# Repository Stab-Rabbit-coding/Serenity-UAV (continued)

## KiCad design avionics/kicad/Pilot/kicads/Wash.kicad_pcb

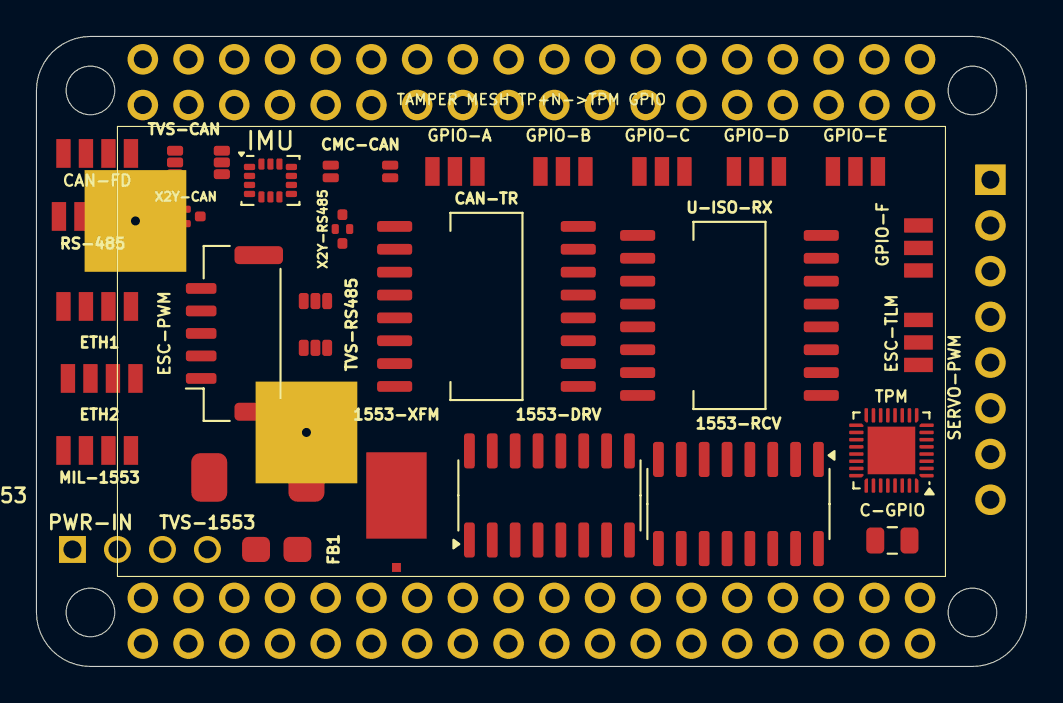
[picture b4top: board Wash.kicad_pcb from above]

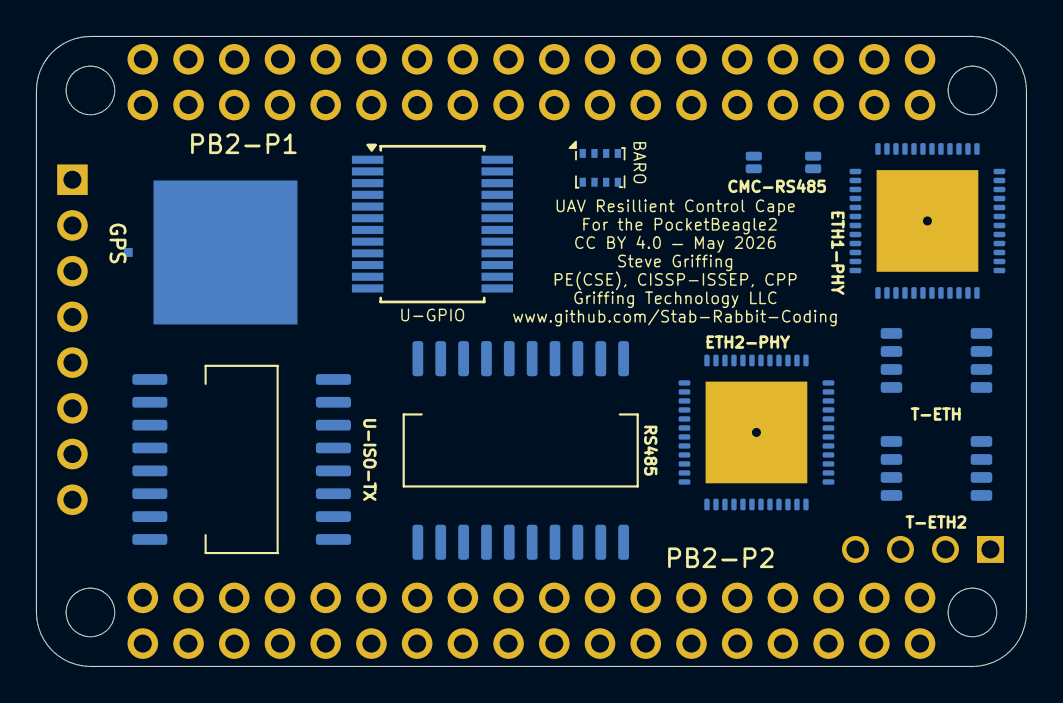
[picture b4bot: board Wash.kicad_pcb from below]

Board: 4 copper layers, 55.0 x 35.0 mm, 42 parts (12 on the bottom side), 83 nets, no tracks yet.

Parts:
1553-DRV: DS26LV31; SOIC-16_3.9x9.9mm_P1.27mm
1553-RCV: DS26LV32; SOIC-16_3.9x9.9mm_P1.27mm
1553-XFM: SM-1553-11; Package
BARO: BMP388; Bosch_LGA-8_2x2.5mm_P0.65mm_ClockwisePinNumbering
C-GPIO: 100nF; C_0805_2012Metric
CAN-FD: JST-GH-4P-CAN; JST_GH_4P
CAN-TR: ISOW1044BDFMR; SOIC-16W_7.5x10.3mm_P1.27mm
CMC-CAN: SRF2012-100Y; Bourns_SRF2012_4T
CMC-RS485: SRF2012-100Y; Bourns_SRF2012_4T
ESC-PWM: JST-GH-5P-ESC; JST_GH_SM05B-GHS-TB_1x05-1MP_P1.25mm_Horizontal
ESC-TLM: JST-GH-3P-ESC-TELEM; JST_GH_3P
ETH1, ETH2: JST-GH-4P-ETH; JST_GH_4P
ETH1-PHY, ETH2-PHY: ADIN1300BCPZ; QFN-48-1EP_7x7mm_P0.5mm_EP5.65x5.65mm
FB1: 742792512; C_0805_2012Metric
GPIO-A: JST-GH-3P-GPIO; JST_GH_3P_V
GPIO-B: JST-GH-3P-GPIO; JST_GH_3P_V
GPIO-C: JST-GH-3P-GPIO; JST_GH_3P_V
GPIO-D: JST-GH-3P-GPIO; JST_GH_3P_V
GPIO-E: JST-GH-3P-GPIO; JST_GH_3P_V
GPIO-F: JST-GH-3P-GPIO; JST_GH_3P_V
GPS: SAM-M10Q-00B; Package
IMU: ICM-42688-P; LGA-14_3x2.5mm_P0.5mm_LayoutBorder3x4y
MIL-1553: JST-GH-4P-1553; JST_GH_4P
PB2-P1: PB2I-P1-2x18; 2x18_P1_Socket
PB2-P2: PB2I-P2-2x18; 2x18_P2_Socket
PWR-IN: Nano-Fit-4P-POWER; Connector_Molex_NanoFit
RS485: ADM2795EBRWZ; SOIC-20W_7.5x12.8mm_P1.27mm
RS-485: JST-GH-4P-RS485; JST_GH_4P
SERVO-PWM: 1x8-SERVO-PWM; Connector_PinHeader_2.54mm
T-ETH, T-ETH2: 749010012A; ETH_XFMR_8P_5x3.5mm
TPM: SLB9670; QFN-32-1EP_4x4mm_P0.4mm_EP2.65x2.65mm
TVS-1553: SMAJ33CA; DO-214AC_SMA
TVS-CAN: PRTR5V0U2X; SOT-363_SC-88
TVS-RS485: PRTR5V0U2X; SOT-363_SC-88
U-GPIO: PCA9555DB; SSOP-24_5.3x8.2mm_P0.65mm
U-ISO-RX: ISO7642FDWRR; SOIC-16W_7.5x10.3mm_P1.27mm
U-ISO-TX: ISO7642FDWRR; SOIC-16W_7.5x10.3mm_P1.27mm
X2Y-CAN, X2Y-RS485: 4.7nF X2Y; X2Y_Cap_4T_0402

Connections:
+3V3: C-GPIO.1, CAN-FD.4, CAN-TR.1, CAN-TR.9, ETH1-PHY.11, ETH1-PHY.20, ETH1-PHY.25, ETH1-PHY.31, ETH1-PHY.40, ETH2-PHY.11, ETH2-PHY.20, ETH2-PHY.25, ETH2-PHY.31, ETH2-PHY.40, GPIO-A.2, GPIO-B.2, GPIO-C.2, GPIO-D.2, GPIO-E.2, GPIO-F.2, PB2-P1.33, PB2-P1.34, RS485.1, RS-485.4, TPM.8, TPM.22, U-GPIO.24, U-ISO-RX.16, U-ISO-TX.1
+5V: FB1.1, FB1.2, PB2-P1.35, PB2-P2.35, PWR-IN.1, PWR-IN.2
CAN_H: CAN-FD.2, CMC-CAN.1, CMC-CAN.3, TVS-CAN.1
CAN_L: CAN-FD.3, CMC-CAN.2, CMC-CAN.4, TVS-CAN.3
CAN_STB: CAN-TR.4, PB2-P1.14
DSHOT0: ESC-PWM.1, PB2-P1.6
DSHOT1: ESC-PWM.2, PB2-P1.5
DSHOT2: ESC-PWM.3, PB2-P1.4
DSHOT3: ESC-PWM.4, PB2-P1.3
DVDD_0P9_ETH1-PHY: ETH1-PHY.4, ETH1-PHY.28, ETH1-PHY.36
DVDD_0P9_ETH2-PHY: ETH2-PHY.4, ETH2-PHY.28, ETH2-PHY.36
ETH2_RXN: ETH2-PHY.15, T-ETH2.8
ETH2_RXP: ETH2-PHY.14, T-ETH2.6
ETH2_TXN: ETH2-PHY.13, T-ETH2.3
ETH2_TXP: ETH2-PHY.12, T-ETH2.1
ETH_RXN: ETH1-PHY.15, T-ETH.8
ETH_RXP: ETH1-PHY.14, T-ETH.6
ETH_TXN: ETH1-PHY.13, T-ETH.3
ETH_TXP: ETH1-PHY.12, T-ETH.1
GND: C-GPIO.2, CAN-FD.1, CAN-TR.6, CAN-TR.10, ESC-PWM.5, ESC-TLM.1, ETH1-PHY.5, ETH1-PHY.41, ETH2-PHY.5, ETH2-PHY.41, GPIO-A.1, GPIO-B.1, GPIO-C.1, GPIO-D.1, GPIO-E.1, GPIO-F.1, GPS.1, PB2-P1.1, PB2-P1.2, PB2-P1.36, PB2-P2.36, PWR-IN.3, PWR-IN.4, RS485.2, RS485.8, RS-485.1, TPM.2, TPM.9, TPM.23, TPM.32, TPM.33, TVS-1553.1, U-GPIO.2, U-GPIO.3, U-GPIO.12, U-GPIO.21, U-ISO-RX.9, U-ISO-TX.8, X2Y-CAN.1, X2Y-CAN.2, X2Y-CAN.3, X2Y-RS485.1, X2Y-RS485.2, X2Y-RS485.3
GND2_CAN: CAN-TR.11, CAN-TR.15, CAN-TR.16, TVS-CAN.2, X2Y-CAN.4
GND2_ETH: U-ISO-RX.8, U-ISO-TX.9
GND2_RS485: RS485.9, RS485.10, RS485.12, RS485.15, TVS-RS485.2, X2Y-RS485.4
GPIO_EXP_A: GPIO-A.3, U-GPIO.4
GPIO_EXP_B: GPIO-B.3, U-GPIO.5
GPIO_EXP_C: GPIO-C.3, U-GPIO.6
GPIO_EXP_D: GPIO-D.3, U-GPIO.7
GPIO_EXP_E: GPIO-E.3, U-GPIO.8
GPIO_EXP_F: GPIO-F.3, U-GPIO.9
I2C1_SCL: PB2-P1.28, U-GPIO.22
I2C1_SDA: PB2-P1.27, U-GPIO.23
IMU_INT2: IMU.14, PB2-P1.18
MCAN0_RX: CAN-TR.5, PB2-P1.15
MCAN0_TX: CAN-TR.3, PB2-P1.16
MDC: ETH1-PHY.23, ETH2-PHY.23, U-ISO-TX.6, U-ISO-TX.11
MDIO: ETH1-PHY.24, ETH2-PHY.24, U-ISO-RX.7, U-ISO-RX.10
PHY1_INTRN: ETH1-PHY.22, PB2-P2.16, U-ISO-RX.6, U-ISO-RX.11
PHY1_RSTN: ETH1-PHY.7, PB2-P2.15, U-ISO-TX.7, U-ISO-TX.10
PHY2_INTRN: ETH2-PHY.22, PB2-P2.14
PHY2_RSTN: ETH2-PHY.7, PB2-P2.13
PRU_1553_RX_N: 1553-RCV.13, PB2-P1.7
PRU_1553_TX_N: 1553-DRV.6, PB2-P1.9
PRU_1553_TX_P: 1553-DRV.10, PB2-P1.10
RMII0_CRS_DV: ETH1-PHY.35, PB2-P2.29, U-ISO-RX.4, U-ISO-RX.13
RMII0_REF_CLK: ETH1-PHY.9, PB2-P2.27, U-ISO-TX.2, U-ISO-TX.15
RMII0_RXD0: ETH1-PHY.33, PB2-P2.31, U-ISO-RX.2, U-ISO-RX.15
RMII0_RXD1: ETH1-PHY.32, PB2-P2.30, U-ISO-RX.3, U-ISO-RX.14
RMII0_RX_ER: ETH1-PHY.27, PB2-P2.28, U-ISO-RX.5, U-ISO-RX.12
RMII0_TXD0: ETH1-PHY.39, PB2-P2.34, U-ISO-TX.3, U-ISO-TX.14
RMII0_TXD1: ETH1-PHY.1, PB2-P2.33, U-ISO-TX.4, U-ISO-TX.13
RMII0_TX_EN: ETH1-PHY.37, PB2-P2.32, U-ISO-TX.5, U-ISO-TX.12
RMII1_CRS_DV: ETH2-PHY.35, PB2-P2.21
RMII1_REF_CLK: ETH2-PHY.9, PB2-P2.19
RMII1_RXD0: ETH2-PHY.33, PB2-P2.23
RMII1_RXD1: ETH2-PHY.32, PB2-P2.22
RMII1_RX_ER: ETH2-PHY.27, PB2-P2.20
RMII1_TXD0: ETH2-PHY.39, PB2-P2.26
RMII1_TXD1: ETH2-PHY.1, PB2-P2.25
RMII1_TX_EN: ETH2-PHY.37, PB2-P2.24
RS485_A: CMC-RS485.1, CMC-RS485.3, RS485.11, RS-485.2, TVS-RS485.1
RS485_B: CMC-RS485.2, CMC-RS485.4, RS485.14, RS-485.3, TVS-RS485.3
RS485_DE: PB2-P1.11, RS485.4, RS485.5
RS485_RX: PB2-P1.12, RS485.6
RS485_TX: PB2-P1.13, RS485.3
SERVO0: PB2-P2.8, SERVO-PWM.1
SERVO1: PB2-P2.7, SERVO-PWM.2
SERVO2: PB2-P2.6, SERVO-PWM.3
SERVO3: PB2-P2.5, SERVO-PWM.4
SERVO4: PB2-P2.4, SERVO-PWM.5
SERVO5: PB2-P2.3, SERVO-PWM.6
SPI0_CLK: BARO.6, IMU.2, PB2-P1.25, TPM.19
SPI0_CS_BARO: BARO.7, PB2-P1.22
SPI0_CS_IMU: IMU.3, PB2-P1.26
SPI0_CS_TPM: PB2-P1.21, TPM.20
SPI0_MISO: BARO.3, IMU.5, PB2-P1.23, TPM.24
SPI0_MOSI: BARO.5, IMU.1, PB2-P1.24, TPM.21
TPM_IRQN: PB2-P2.12, TPM.18
TPM_RSTN: PB2-P2.11, TPM.17
UART_ESC_RX: ESC-TLM.3, PB2-P1.29
UART_ESC_TX: ESC-TLM.2, PB2-P1.30
VCC2_CAN: CAN-TR.12, CAN-TR.13, TVS-CAN.5
VCC2_ETH: U-ISO-RX.1, U-ISO-TX.16
VCC2_RS485: RS485.13, RS485.16, TVS-RS485.5

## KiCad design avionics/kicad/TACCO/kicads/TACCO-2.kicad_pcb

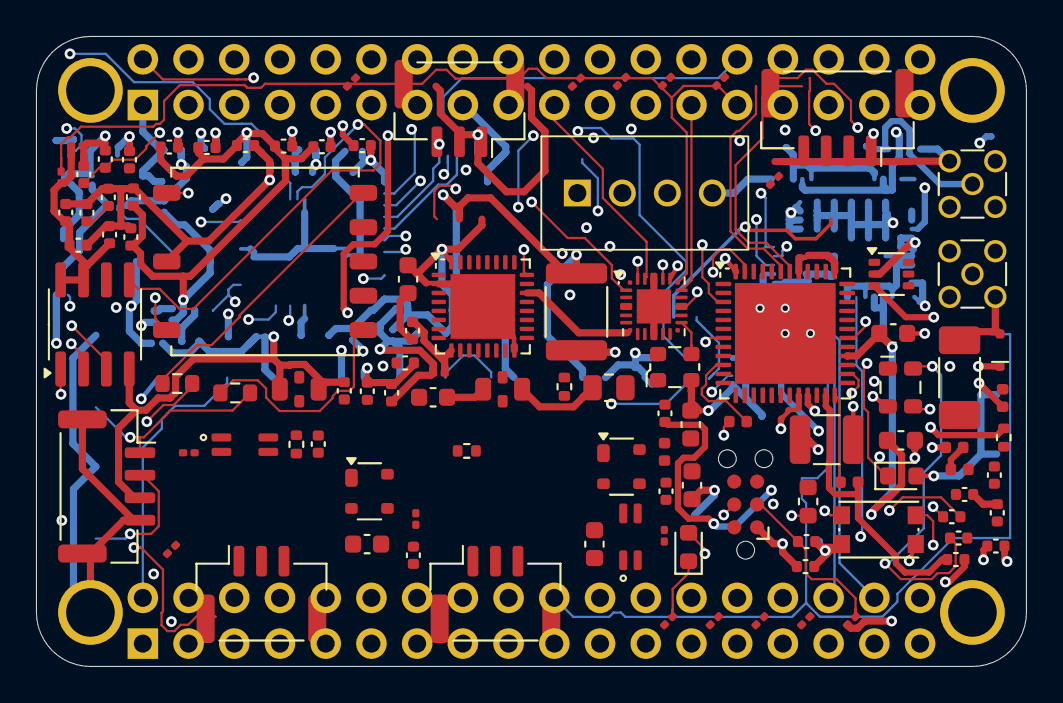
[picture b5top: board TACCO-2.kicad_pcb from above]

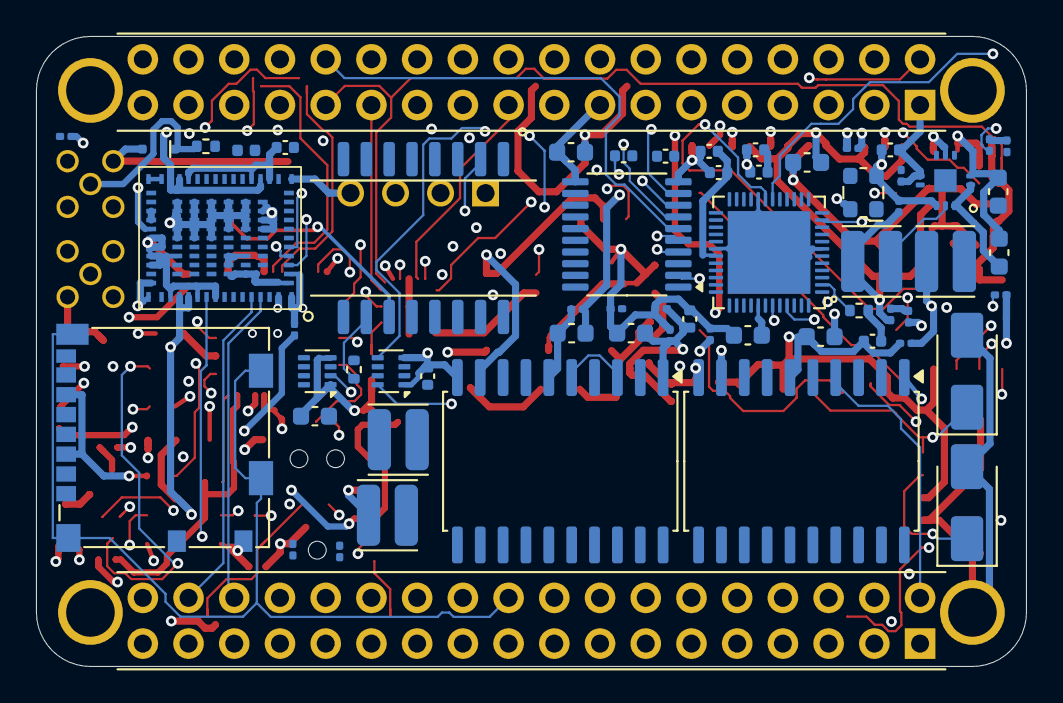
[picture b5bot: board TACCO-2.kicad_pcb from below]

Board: 6 copper layers, 55.0 x 35.0 mm, 170 parts (62 on the bottom side), 142 nets.

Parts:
1553-XCVR: HI-6138PCIF; Holt_HI-6138_QFN-48_6x6mm_P0.4mm_EP4.6mm
1553-XFM: PM-DB2791S; Xfmr_1553_SMD_0.40in_8pin
C-1V8RF-HF, C-3V3-HF, C-25M, C-50M, C-485-3, C-485-6, C-1553A, C-1553B, C-1553D: 100nF; C_0402_1005Metric
C-1V8RF-IN, C-3V3-IN, C-485-2, C-485-5: 10uF 10V X5R; C_0603_1608Metric
C-1V8RF-O1, C-1V8RF-O2, C-3V3-O1, C-3V3-O2: 22uF 6.3V X5R; C_0603_1608Metric
C-485-1, C-485-4: 10nF; C_0201_0603Metric
C-1553C: 10uF 6.3V X5R; C_0603_1608Metric
C-ANT-SANT: 10pF; C_0201_0603Metric
C-ANT-SH1, C-ANT-SH2: DNP; C_0402_1005Metric
C-BS: 10nF 2kV; C_1808_4520Metric
C-BST, C-BST18: 100nF; C_0402_1005Metric
C-CAN1, C-CAN4: 10nF; C_0201_0603Metric
C-CAN2, C-CAN5: 10uF 10V X5R; C_0603_1608Metric
C-CAN3, C-CAN6: 100nF; C_0402_1005Metric
C-FLASH1: 100nF; C_0402_1005Metric
C-IN1: 47uF 10V X5R; C_1210_3225Metric
C-IN2: 10uF 10V X5R; C_0603_1608Metric
C-IN3: 100nF; C_0402_1005Metric
C-MLRS-BULK: 4.7uF; C_0603_1608Metric
C-MLRS-HSE: 10pF C0G; C_0402_1005Metric
C-MLRS-RST: 100nF; C_0402_1005Metric
C-MLRS-RX1: VERIFY AN5457; C_0402_1005Metric
C-MLRS-RXN: VERIFY AN5457; C_0402_1005Metric
C-MLRS-RXP: VERIFY AN5457; C_0402_1005Metric
C-MLRS-SH1, C-MLRS-SH2: DNP; C_0201_0603Metric
C-MLRS-SMPS: 100nF; C_0402_1005Metric
C-MLRS-TCXO: 100nF; C_0402_1005Metric
C-MLRS-TX0, C-MLRS-TX1, C-MLRS-TX2: VERIFY AN5457; C_0402_1005Metric
C-MLRS-VBAT: 100nF; C_0402_1005Metric
C-MLRS-VDD1, C-MLRS-VDD2: 100nF; C_0402_1005Metric
C-MLRS-VDDA1: 100nF; C_0402_1005Metric
C-MLRS-VDDA2: 1uF; C_0402_1005Metric
C-MLRS-VDDPA1: 100nF; C_0402_1005Metric
C-MLRS-VDDPA2: 4.7uF; C_0603_1608Metric
C-MLRS-VDDRF: 100nF; C_0402_1005Metric
C-MLRS-VFB: 470nF; C_0402_1005Metric
C-MLRS-VRPA: 100nF VERIFY AN5457; C_0402_1005Metric
C-PHY-A1: 10nF; C_0201_0603Metric
C-PHY-A2: 100nF; C_0402_1005Metric
C-PHY-A3: 1uF; C_0402_1005Metric
C-PHY-CRD1: 100nF; C_0402_1005Metric
C-PHY-CRD2: 1uF; C_0402_1005Metric
C-PHY-CTD1: 100nF; C_0402_1005Metric
C-PHY-CTD2: 1uF; C_0402_1005Metric
C-PLD1: 100nF; C_0402_1005Metric
C-RF-IN1: 10uF 10V X5R; C_0603_1608Metric
C-RF-IN2: 100nF; C_0402_1005Metric
C-RF-O1, C-RF-O2: 22uF 6.3V X5R; C_0603_1608Metric
C-SS, C-SS18: 10nF; C_0201_0603Metric
C-TPM1: 1uF; C_0402_1005Metric
C-TPM2, C-TPM3, C-TPM4: 100nF 6.3V X5R; C_0201_0603Metric
C-ZB-18-1, C-ZB-18-2, C-ZB-33-1, C-ZB-33-2: 100nF 6.3V X5R; C_0201_0603Metric
C-ZB-SDVIO: 100nF 6.3V X5R; C_0201_0603Metric
C-ZB-VIO: 100nF 6.3V X5R; C_0201_0603Metric
CAN-TR: ISOW1044BDFMR; SOIC-20W_7.5x12.8mm_P1.27mm
CMC-CAN: SRF2012-100Y; Bourns_SRF2012_4T
CMC-RS485: SRF2012-100Y; Bourns_SRF2012_4T
D-ANT-MLRS: RCLAMP0502B; RCLAMP0502B_SOD882
D-ANT-RADIO: RCLAMP0502B; RCLAMP0502B_SOD882
ETH-PHY: DP83825IRHBR; Texas_RMQ0024A_WQFN-24-1EP_3x3mm_P0.4mm_EP1.9x1.9mm
FB1: 742792510; L_1812_4532Metric
FB-MLRS-1, FB-MLRS-2: 600R@100MHz 0402; L_0402_1005Metric
H1, H2, H3, H4: M2.5 PGND; MountingHole_2.7mm_M2.5_PGND_Ring
J-485: SM03B-GHS-TB; JST_GH_SM03B-GHS-TB_1x03-1MP_P1.25mm_Horizontal
J-1553: SM04B-GHS-TB; JST_GH_SM04B-GHS-TB_1x04-1MP_P1.25mm_Horizontal
J-ANT-MLRS: MMCX vertical; MMCX_Molex_73415-1471_Vertical
J-ANT-RADIO: MMCX vertical; MMCX_Molex_73415-1471_Vertical
J-CAN: SM03B-GHS-TB; JST_GH_SM03B-GHS-TB_1x03-1MP_P1.25mm_Horizontal
J-ETH: SM04B-GHS-TB; JST_GH_SM04B-GHS-TB_1x04-1MP_P1.25mm_Horizontal
J-FAN: SM03B-GHS-TB; JST_GH_SM03B-GHS-TB_1x03-1MP_P1.25mm_Horizontal
J-MLRS-SWD: TC2030-IDC-NL pads; Tag-Connect_TC2030-IDC-NL_2x03_P1.27mm_Vertical
J-SD: microSD push-pull; microSD_HC_Molex_104031-0811
L-1V8RF, L-3V3: 3.3uH 2.25A; L_WE-MAPI_3015
L-ANT-SER: 0R link; R_0402_1005Metric
L-MLRS-PA: VERIFY AN5457; L_0402_1005Metric
L-MLRS-RX1, L-MLRS-RX2: VERIFY AN5457; L_0402_1005Metric
L-MLRS-SER: 0R link; R_0402_1005Metric
L-MLRS-SMPS: 15uH; L_0603_1608Metric
L-MLRS-TX1, L-MLRS-TX2: VERIFY AN5457; L_0402_1005Metric
L-RF1, L-RF2: 2.2uH 3A; L_Wuerth_MAPI-3015
LED-MLRS-G: Green; LED_0603_1608Metric
LED-MLRS-R: Red; LED_0603_1608Metric
MLRS-MCU: STM32WLE5JCU6; QFN-48-1EP_7x7mm_P0.5mm_EP5.6x5.6mm
NOR-FLASH: W25Q128JVSIQ; SOIC-8_3.9x4.9mm_P1.27mm
PB2-P1: PB2I-P1-2x18; PocketBeagle2_2x18_P1_Socket
PB2-P2: PB2I-P2-2x18; PocketBeagle2_2x18_P2_Socket
PWR-IN: Nano-Fit 4P; Molex_NanoFit_1x04_Horizontal
R-485T: 120R; R_0402_1005Metric
R-1553IRQ: 10k; R_0402_1005Metric
R-1553N, R-1553P: 55R 2%; R_0603_1608Metric
R-AD0: 2.49k; R_0201_0603Metric
R-BSR: 75R; R_0402_1005Metric
R-BST: 75R; R_0402_1005Metric
R-CANT: 120R; R_0402_1005Metric
R-EN3, R-EN18: 100k; R_0201_0603Metric
R-FB3H: 100k 1%; R_0201_0603Metric
R-FB3L, R-FB18L: 32.4k 1%; R_0201_0603Metric
R-FB18H: 40.2k 1%; R_0201_0603Metric
R-FLASH-WP: 10k; R_0201_0603Metric
R-MLRS-BOOT0: 10k; R_0201_0603Metric
R-MLRS-LEDG: 1k; R_0201_0603Metric
R-MLRS-LEDR: 1k; R_0201_0603Metric
R-MLRS-RST: 22k; R_0201_0603Metric
R-MLRS-SWCLK: 22R; R_0201_0603Metric
R-MLRS-SWDIO: 22R; R_0201_0603Metric
R-PGND: 0R; R_0805_2012Metric
R-RBIAS: 6.49k 1%; R_0201_0603Metric
R-TPM10: 10k; R_0201_0603Metric
R-TPMCS: 10k; R_0201_0603Metric
RFSW-MLRS: PE4259; SOT-363_SC-70-6
RS485: ISOW1412DFMR; SOIC-20W_7.5x12.8mm_P1.27mm
SD-WB: ATF16V8BQL-15XI; TSSOP-20_4.4x6.5mm_P0.65mm
SW-MLRS: KMR2 tact; SW_Push_1P1T_NO_CK_KMR2
T-ETH: 749010012A; Wurth_749010012A_WE-LAN
TPM: SLB9672XU20; QFN-32-1EP_5x5mm_P0.5mm_EP3.6x3.6mm
TVS-1553N, TVS-1553P: SMAJ33CA; D_SMA
TVS-CAN: PRTR5V0U2X; SOT-143
TVS-RS485: PRTR5V0U2X; SOT-143
U-1V8RF, U-3V3: TPS62933DRLR; SOT-583-8
U-3V3RF: TPS63031DSKR; TPS6303x_VSON-10_2p5
WIFI-BT-ZB: LBES5PL2EL-923; Murata_Type2EL_LGA107
X2Y-CAN, X2Y-RS485: 4.7nF X2Y; X2Y_0805_4T
X-25M: 25MHz 3.3V; Oscillator_SMD_ECS_2520MV-xxx-xx-4Pin_2.5x2.0mm
X-50M: 50MHz 3.3V; Oscillator_SMD_ECS_2520MV-xxx-xx-4Pin_2.5x2.0mm
X-MLRS: TG2520SMN 32MHz 1.8V clipped-sine; Oscillator_SMD_SeikoEpson_TG2520SMN-xxx-xxxxxx-4Pin_2.5x2.0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

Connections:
+1V8_RF: C-1V8RF-O1.1, C-1V8RF-O2.1, C-ZB-18-1.1, C-ZB-18-2.1, C-ZB-SDVIO.1, L-1V8RF.2, R-FB18H.1, WIFI-BT-ZB.30, WIFI-BT-ZB.31, WIFI-BT-ZB.40
+3V3: 1553-XCVR.6, 1553-XCVR.16, 1553-XCVR.31, 1553-XCVR.41, 1553-XCVR.44, C-3V3-O1.1, C-3V3-O2.1, C-25M.1, C-50M.1, C-485-3.1, C-1553A.1, C-1553B.1, C-1553C.1, C-1553D.1, C-CAN3.1, C-FLASH1.1, C-PHY-A1.1, C-PHY-A2.1, C-PHY-A3.1, C-PLD1.1, C-TPM1.1, C-TPM2.1, C-TPM3.1, C-TPM4.1, C-ZB-VIO.1, CAN-TR.1, ETH-PHY.6, ETH-PHY.19, J-SD.4, L-3V3.2, NOR-FLASH.7, NOR-FLASH.8, R-1553IRQ.1, R-AD0.1, R-FB3H.1, R-FLASH-WP.1, R-TPM10.1, R-TPMCS.1, RS485.1, RS485.8, SD-WB.20, TPM.1, TPM.14, TPM.22, U-3V3RF.6, WIFI-BT-ZB.24, WIFI-BT-ZB.25, WIFI-BT-ZB.54, WIFI-BT-ZB.55, WIFI-BT-ZB.56, X-25M.4, X-50M.4
+3V3_PB2: PB2-P1.14, PB2-P2.23
+3V3_RF: C-MLRS-BULK.1, C-MLRS-SMPS.1, C-MLRS-VBAT.1, C-MLRS-VDD1.1, C-MLRS-VDD2.1, C-MLRS-VDDA1.1, C-MLRS-VDDA2.1, C-MLRS-VDDPA1.1, C-MLRS-VDDPA2.1, C-MLRS-VDDRF.1, C-RF-O1.1, C-RF-O2.1, C-ZB-33-1.1, C-ZB-33-2.1, J-MLRS-SWD.1, L-RF2.2, MLRS-MCU.11, MLRS-MCU.25, MLRS-MCU.28, MLRS-MCU.37, MLRS-MCU.41, MLRS-MCU.44, MLRS-MCU.46, R-MLRS-LEDR.1, R-MLRS-RST.1, U-3V3RF.1, U-3V3RF.10, WIFI-BT-ZB.12, WIFI-BT-ZB.13
+5V: C-1V8RF-HF.1, C-1V8RF-IN.1, C-3V3-HF.1, C-3V3-IN.1, C-485-1.1, C-485-2.1, C-CAN1.1, C-CAN2.1, C-IN2.1, C-IN3.1, C-RF-IN1.1, C-RF-IN2.1, CAN-TR.9, FB1.2, J-FAN.2, L-RF1.2, PB2-P1.1, PB2-P1.7, R-EN3.1, R-EN18.1, RS485.9, U-1V8RF.3, U-3V3.3, U-3V3RF.5, U-3V3RF.8
+5V_IN: C-IN1.1, FB1.1, PWR-IN.1, PWR-IN.2
BST_1V8RF: C-BST18.1, U-1V8RF.6
BST_3V3: C-BST.1, U-3V3.6
BT_UART_CTS: PB2-P1.10, WIFI-BT-ZB.50
BT_UART_RTS: PB2-P1.12, WIFI-BT-ZB.52
BT_UART_RX: PB2-P1.6, WIFI-BT-ZB.51
BT_UART_TX: PB2-P1.8, WIFI-BT-ZB.49
BUS_1553_B_N: J-1553.2, R-1553N.2, TVS-1553N.1
BUS_1553_B_P: J-1553.1, R-1553P.2, TVS-1553P.1
CAN_B_H: CAN-TR.19, CMC-CAN.1
CAN_B_H_F: CMC-CAN.2, J-CAN.1, R-CANT.1, TVS-CAN.1
CAN_B_L: CAN-TR.18, CMC-CAN.4
CAN_B_L_F: CMC-CAN.3, J-CAN.2, R-CANT.2, TVS-CAN.3
CAN_B_STB: CAN-TR.4, PB2-P2.2
ETH-PHY_RBIAS: ETH-PHY.14, R-RBIAS.1
ETHB_BS: C-BS.1, R-BSR.2, R-BST.2
ETHB_CRD: C-PHY-CRD1.1, C-PHY-CRD2.1, T-ETH.7
ETHB_CTD: C-PHY-CTD1.1, C-PHY-CTD2.1, T-ETH.2
ETHB_LINE_CRX: R-BSR.1, T-ETH.10
ETHB_LINE_CTX: R-BST.1, T-ETH.15
ETHB_LINE_RXN: J-ETH.4, T-ETH.9
ETHB_LINE_RXP: J-ETH.3, T-ETH.11
ETHB_LINE_TXN: J-ETH.2, T-ETH.14
ETHB_LINE_TXP: J-ETH.1, T-ETH.16
ETHB_RXN: ETH-PHY.7, T-ETH.8
ETHB_RXP: ETH-PHY.8, T-ETH.6
ETHB_TXN: ETH-PHY.10, T-ETH.3
ETHB_TXP: ETH-PHY.11, T-ETH.1
FAN_PWM_B: J-FAN.3, PB2-P1.36
FB_1V8RF: R-FB18H.2, R-FB18L.1, U-1V8RF.8
FB_3V3: R-FB3H.2, R-FB3L.1, U-3V3.8
FLASH_WP_N: NOR-FLASH.3, R-FLASH-WP.2, SD-WB.19
GND: 1553-XCVR.7, 1553-XCVR.20, 1553-XCVR.30, 1553-XCVR.49, 1553-XFM.2, C-1V8RF-HF.2, C-1V8RF-IN.2, C-1V8RF-O1.2, C-1V8RF-O2.2, C-3V3-HF.2, C-3V3-IN.2, C-3V3-O1.2, C-3V3-O2.2, C-25M.2, C-50M.2, C-485-1.2, C-485-2.2, C-485-3.2, C-1553A.2, C-1553B.2, C-1553C.2, C-1553D.2, C-ANT-SH1.2, C-ANT-SH2.2, C-CAN1.2, C-CAN2.2, C-CAN3.2, C-FLASH1.2, C-IN1.2, C-IN2.2, C-IN3.2, C-MLRS-BULK.2, C-MLRS-RST.2, C-MLRS-RX1.2, C-MLRS-SH1.2, C-MLRS-SH2.2, C-MLRS-SMPS.2, C-MLRS-TCXO.2, C-MLRS-TX1.2, C-MLRS-TX2.2, C-MLRS-VBAT.2, C-MLRS-VDD1.2, C-MLRS-VDD2.2, C-MLRS-VDDA1.2, C-MLRS-VDDA2.2, C-MLRS-VDDPA1.2, C-MLRS-VDDPA2.2, C-MLRS-VDDRF.2, C-MLRS-VFB.2, C-MLRS-VRPA.2, C-PHY-A1.2, C-PHY-A2.2, C-PHY-A3.2, C-PHY-CRD1.2, C-PHY-CRD2.2, C-PHY-CTD1.2, C-PHY-CTD2.2, C-PLD1.2, C-RF-IN1.2, C-RF-IN2.2, C-RF-O1.2, C-RF-O2.2, C-SS.2, C-SS18.2, C-TPM1.2, C-TPM2.2, C-TPM3.2, C-TPM4.2, C-ZB-18-1.2, C-ZB-18-2.2, C-ZB-33-1.2, C-ZB-33-2.2, C-ZB-SDVIO.2, C-ZB-VIO.2, CAN-TR.6, CAN-TR.10, ETH-PHY.9, ETH-PHY.21, ETH-PHY.25, J-1553.3, J-FAN.1, J-MLRS-SWD.5, J-SD.3, J-SD.6, J-SD.10, L-MLRS-RX2.2, LED-MLRS-G.2, MLRS-MCU.48, MLRS-MCU.49, NOR-FLASH.4, PB2-P1.15, PB2-P1.16, PB2-P1.22, PB2-P2.15, PB2-P2.21, PWR-IN.3, PWR-IN.4, R-FB3L.2, R-FB18L.2, R-MLRS-BOOT0.2, R-PGND.1, R-RBIAS.2, RFSW-MLRS.2, RS485.6, RS485.10, SD-WB.10, SD-WB.11, SW-MLRS.2, TPM.2, TPM.9, TPM.16, TPM.23, TPM.32, TPM.33, U-1V8RF.1, U-1V8RF.4, U-3V3.1, U-3V3.4, U-3V3RF.3, U-3V3RF.7, U-3V3RF.9, WIFI-BT-ZB.1, WIFI-BT-ZB.2, WIFI-BT-ZB.9, WIFI-BT-ZB.11, WIFI-BT-ZB.14, WIFI-BT-ZB.16, WIFI-BT-ZB.17, WIFI-BT-ZB.19, WIFI-BT-ZB.20, WIFI-BT-ZB.21, WIFI-BT-ZB.22, WIFI-BT-ZB.28, WIFI-BT-ZB.29, WIFI-BT-ZB.32, WIFI-BT-ZB.39, WIFI-BT-ZB.41, WIFI-BT-ZB.43, WIFI-BT-ZB.53, WIFI-BT-ZB.62, WIFI-BT-ZB.67, WIFI-BT-ZB.68, WIFI-BT-ZB.71, WIFI-BT-ZB.81, WIFI-BT-ZB.82, WIFI-BT-ZB.83, WIFI-BT-ZB.84, WIFI-BT-ZB.85, WIFI-BT-ZB.86, WIFI-BT-ZB.87, WIFI-BT-ZB.88, WIFI-BT-ZB.89, WIFI-BT-ZB.90, WIFI-BT-ZB.91, WIFI-BT-ZB.92, WIFI-BT-ZB.93, WIFI-BT-ZB.94, WIFI-BT-ZB.95, WIFI-BT-ZB.96, WIFI-BT-ZB.97, WIFI-BT-ZB.98, WIFI-BT-ZB.99, WIFI-BT-ZB.100, WIFI-BT-ZB.101, WIFI-BT-ZB.102, WIFI-BT-ZB.103, WIFI-BT-ZB.104, WIFI-BT-ZB.105, WIFI-BT-ZB.106, WIFI-BT-ZB.107, X2Y-CAN.1, X2Y-CAN.2, X2Y-RS485.1, X2Y-RS485.2, X-25M.2, X-50M.2, X-MLRS.2
GND2_CANB: C-CAN4.2, C-CAN5.2, C-CAN6.2, CAN-TR.11, CAN-TR.15, CAN-TR.16, CAN-TR.17, J-CAN.3, TVS-CAN.2, X2Y-CAN.3, X2Y-CAN.4
GND2_RS485B: C-485-4.2, C-485-5.2, C-485-6.2, J-485.3, RS485.11, RS485.13, RS485.15, TVS-RS485.2, X2Y-RS485.3, X2Y-RS485.4
M1553B_IRQN: 1553-XCVR.2, PB2-P2.8, R-1553IRQ.2
M1553B_MCLK: 1553-XCVR.21, X-50M.3
M1553B_MRN: 1553-XCVR.23, PB2-P2.10
M1553B_N: 1553-XCVR.43, 1553-XFM.3
M1553B_P: 1553-XCVR.45, 1553-XFM.1
M1553B_SEC_N: 1553-XFM.8, R-1553N.1
M1553B_SEC_P: 1553-XFM.4, R-1553P.1
M1553B_TX_INH: 1553-XCVR.11, PB2-P2.17
MCAN0_B_RX: CAN-TR.5, PB2-P2.7
MCAN0_B_TX: CAN-TR.3, PB2-P2.5
MDC0: ETH-PHY.16, PB2-P2.1
MDIO0: ETH-PHY.15, PB2-P2.3
MLRS_ANT_F: C-MLRS-SH2.1, D-ANT-MLRS.1, J-ANT-MLRS.1, L-MLRS-SER.2
MLRS_ANT_RF: C-MLRS-SH1.1, L-MLRS-SER.1, RFSW-MLRS.5
MLRS_BOOT0: MLRS-MCU.19, R-MLRS-BOOT0.1
MLRS_BTN: MLRS-MCU.7, SW-MLRS.1
MLRS_HSE_IN: C-MLRS-HSE.2, MLRS-MCU.26
MLRS_LEDG_A: LED-MLRS-G.1, R-MLRS-LEDG.2
MLRS_LEDR_A: LED-MLRS-R.1, R-MLRS-LEDR.2
MLRS_LED_G: MLRS-MCU.43, R-MLRS-LEDG.1
MLRS_LED_R: LED-MLRS-R.2, MLRS-MCU.3
MLRS_RFI_N: C-MLRS-RXN.1, MLRS-MCU.21
MLRS_RFI_P: C-MLRS-RXP.1, MLRS-MCU.20
MLRS_RFO_HP: C-MLRS-TX0.1, L-MLRS-PA.2, MLRS-MCU.23
MLRS_RF_RX_EN: MLRS-MCU.12, RFSW-MLRS.4
MLRS_RF_TX_EN: MLRS-MCU.13, RFSW-MLRS.6
MLRS_RST: C-MLRS-RST.1, J-MLRS-SWD.3, MLRS-MCU.18, R-MLRS-RST.2
MLRS_RX1: C-MLRS-RXP.2, L-MLRS-RX1.1
MLRS_RX2: C-MLRS-RXN.2, L-MLRS-RX2.1
MLRS_RX_F: C-MLRS-RX1.1, L-MLRS-RX1.2, RFSW-MLRS.1
MLRS_SWCLK: MLRS-MCU.42, R-MLRS-SWCLK.1
MLRS_SWCLK_HDR: J-MLRS-SWD.4, R-MLRS-SWCLK.2
MLRS_SWDIO: MLRS-MCU.36, R-MLRS-SWDIO.1
MLRS_SWDIO_HDR: J-MLRS-SWD.2, R-MLRS-SWDIO.2
MLRS_TCXO_OUT: C-MLRS-HSE.1, X-MLRS.3
MLRS_TX1: C-MLRS-TX0.2, L-MLRS-TX1.1
MLRS_TX2: C-MLRS-TX1.1, L-MLRS-TX1.2, L-MLRS-TX2.1
MLRS_TX_F: C-MLRS-TX2.1, L-MLRS-TX2.2, RFSW-MLRS.3
MLRS_VDDTCXO: C-MLRS-TCXO.1, MLRS-MCU.30, X-MLRS.4
MLRS_VFB: C-MLRS-VFB.1, L-MLRS-SMPS.2, MLRS-MCU.29, MLRS-MCU.45
MLRS_VLX: L-MLRS-SMPS.1, MLRS-MCU.47
MLRS_VR_PA: C-MLRS-VRPA.1, L-MLRS-PA.1, MLRS-MCU.24
PGND: C-BS.2, D-ANT-MLRS.2, D-ANT-RADIO.2, H1.1, H2.1, H3.1, H4.1, J-485.MP, J-1553.4, J-1553.MP, J-ANT-MLRS.2, J-ANT-RADIO.2, J-CAN.MP, J-ETH.MP, R-PGND.2, TVS-1553N.2, TVS-1553P.2
PHY1_INTRN: ETH-PHY.3, PB2-P2.6
PHY1_RSTN: ETH-PHY.5, PB2-P2.4
PHY_XI_25M: ETH-PHY.13, X-25M.3
PLD_CLK: PB2-P1.13, SD-WB.1
PLD_I1: PB2-P1.20, SD-WB.2
PLD_I2: PB2-P1.21, SD-WB.3
PLD_I3: PB2-P1.23, SD-WB.4
PLD_I4: PB2-P1.26, SD-WB.5
PLD_I5: PB2-P1.28, SD-WB.6
PLD_I6: PB2-P1.29, SD-WB.7
PLD_I7: PB2-P1.31, SD-WB.8
PLD_I8: PB2-P1.33, SD-WB.9
RADIO_ANT1_IN: C-ANT-SANT.2, WIFI-BT-ZB.18
RADIO_ANT1_OUT: C-ANT-SANT.1, WIFI-BT-ZB.23
RADIO_ANT_F: C-ANT-SH2.1, D-ANT-RADIO.1, J-ANT-RADIO.1, L-ANT-SER.2
RADIO_ANT_RF: C-ANT-SH1.1, L-ANT-SER.1, WIFI-BT-ZB.15
RF_SW1: L-RF1.1, U-3V3RF.4
RF_SW2: L-RF2.1, U-3V3RF.2
RMII2_CRS_DV: ETH-PHY.20, PB2-P1.35
RMII2_REF_CLK: ETH-PHY.2, PB2-P1.34
RMII2_RXD0: ETH-PHY.18, PB2-P1.27, R-AD0.2
RMII2_RXD1: ETH-PHY.17, PB2-P1.25
RMII2_RX_ER: ETH-PHY.22, PB2-P1.19
RMII2_TXD0: ETH-PHY.23, PB2-P1.4
RMII2_TXD1: ETH-PHY.24, PB2-P2.31
RMII2_TX_EN: ETH-PHY.1, PB2-P1.2
RS485_B_A: CMC-RS485.1, RS485.17, RS485.20
RS485_B_A_F: CMC-RS485.2, J-485.1, R-485T.1, TVS-RS485.1
RS485_B_B: CMC-RS485.4, RS485.18, RS485.19
RS485_B_B_F: CMC-RS485.3, J-485.2, R-485T.2, TVS-RS485.3
RS485_B_DE: PB2-P2.22, RS485.3, RS485.5
RS485_B_RX: PB2-P2.9, RS485.4
RS485_B_TX: PB2-P2.11, RS485.2
SD_CD: J-SD.11, PB2-P2.20
SPI0_B_CLK: 1553-XCVR.17, NOR-FLASH.6, PB2-P2.29, TPM.19, WIFI-BT-ZB.8
SPI0_B_CS_1553: 1553-XCVR.15, PB2-P2.24
SPI0_B_CS_FLASH: NOR-FLASH.1, PB2-P2.30
SPI0_B_CS_TPM: PB2-P2.36, R-TPMCS.2, TPM.20
SPI0_B_CS_ZB: PB2-P2.32, WIFI-BT-ZB.4
SPI0_B_MISO: 1553-XCVR.18, NOR-FLASH.2, PB2-P2.27, TPM.24, WIFI-BT-ZB.6
SPI0_B_MOSI: 1553-XCVR.19, NOR-FLASH.5, PB2-P2.25, TPM.21, WIFI-BT-ZB.7
SS_1V8RF: C-SS18.1, U-1V8RF.7
SS_3V3: C-SS.1, U-3V3.7
SW_1V8RF: C-BST18.2, L-1V8RF.1, U-1V8RF.5
SW_3V3: C-BST.2, L-3V3.1, U-3V3.5
TPM_B_IRQN: PB2-P2.19, TPM.18
TPM_B_P10_PU: R-TPM10.2, TPM.10
TPM_B_RSTN: PB2-P2.18, TPM.17
U1V8RF_EN: R-EN18.2, U-1V8RF.2
U3V3_EN: R-EN3.2, U-3V3.2
UART_WIOE5_RX: FB-MLRS-1.1, PB2-P1.32
UART_WIOE5_RX_F: FB-MLRS-1.2, MLRS-MCU.10
UART_WIOE5_TX: FB-MLRS-2.1, PB2-P1.30
UART_WIOE5_TX_F: FB-MLRS-2.2, MLRS-MCU.9
VCC2_CANB: C-CAN4.1, C-CAN5.1, C-CAN6.1, CAN-TR.12, CAN-TR.13, CAN-TR.20, TVS-CAN.4
VCC2_RS485B: C-485-4.1, C-485-5.1, C-485-6.1, RS485.12, RS485.16, TVS-RS485.4
WIFI_EN: PB2-P2.28, WIFI-BT-ZB.10
WIFI_IRQ: PB2-P2.33, WIFI-BT-ZB.72
ZB_SPI_INT: PB2-P2.34, WIFI-BT-ZB.5

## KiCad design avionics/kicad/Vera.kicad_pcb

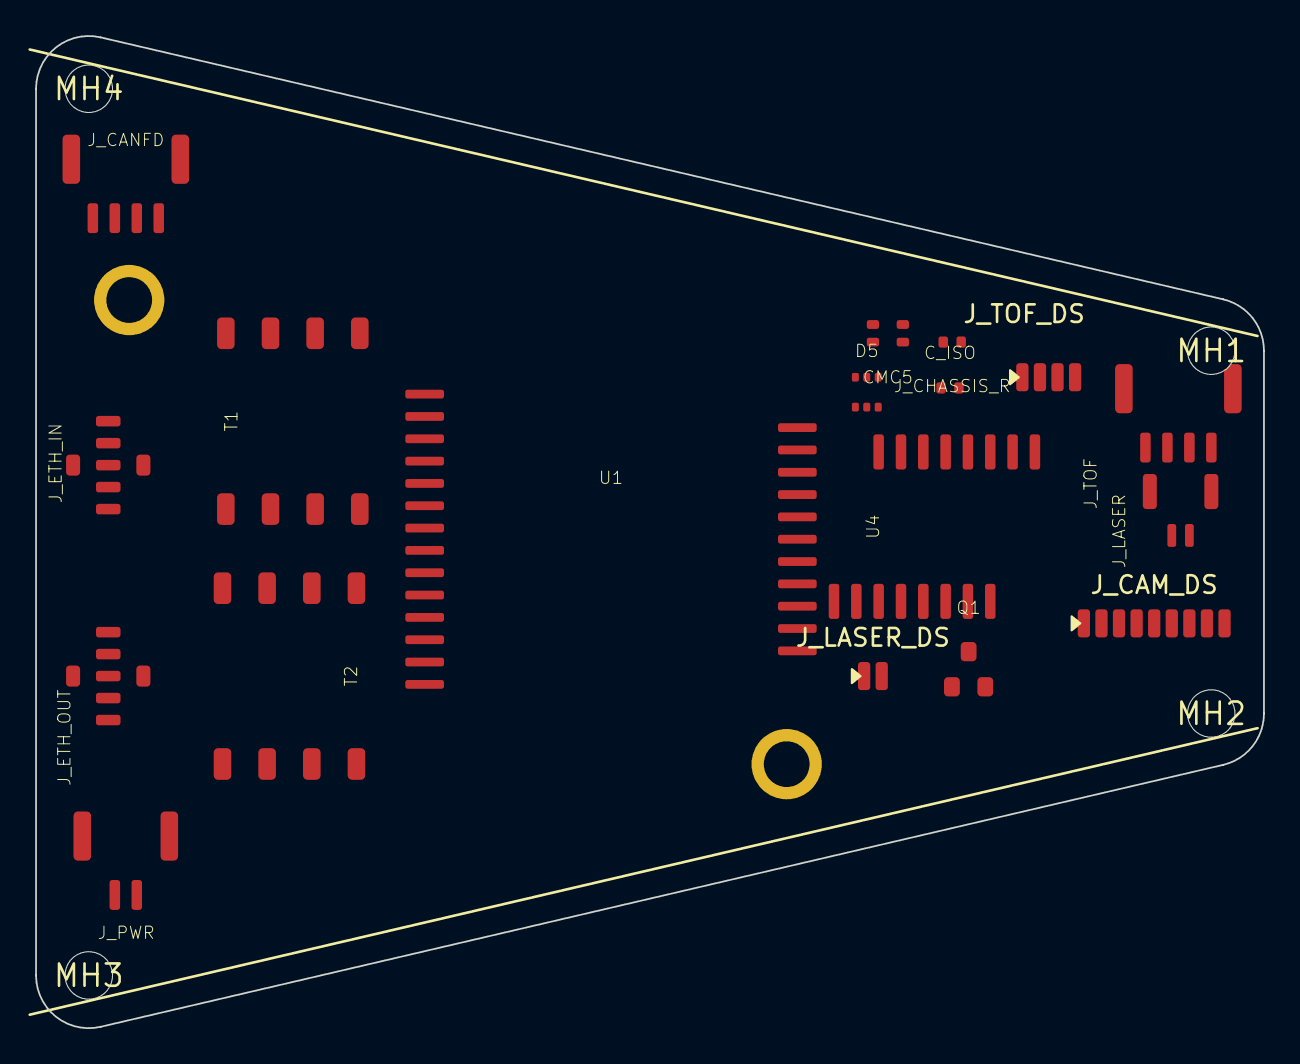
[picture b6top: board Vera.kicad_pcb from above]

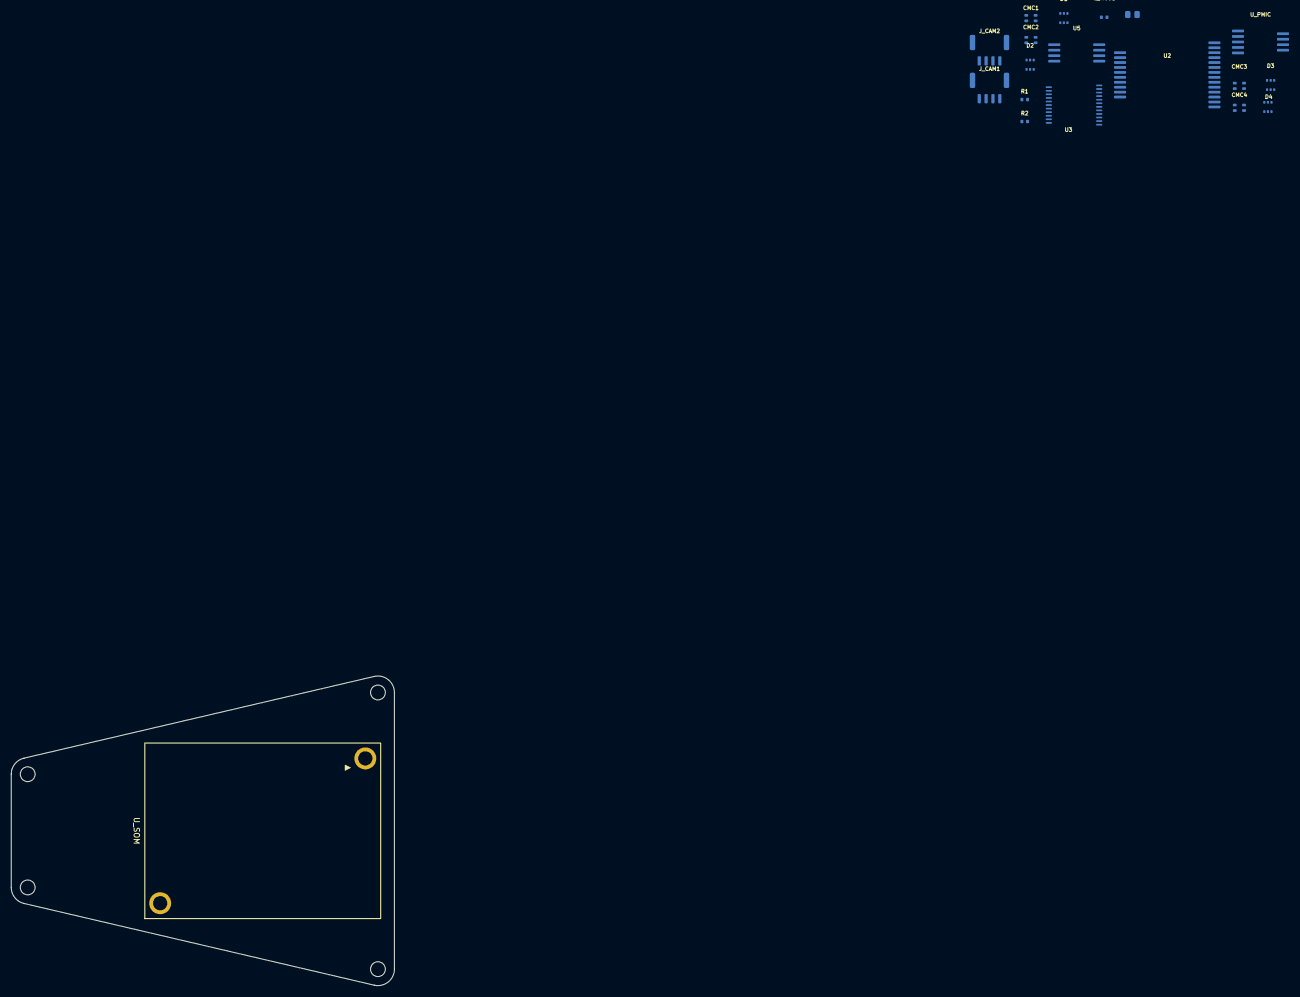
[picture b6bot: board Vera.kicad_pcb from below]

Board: 4 copper layers, 69.8 x 56.4 mm, 41 parts (19 on the bottom side), 68 nets, no tracks yet.

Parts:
CMC1, CMC3: SRF2012-100Y (TX); L_Taiyo-Yuden_NR-20xx
CMC2, CMC4: SRF2012-100Y (RX); L_Taiyo-Yuden_NR-20xx
CMC5: SRF2012-100Y (CAN); L_Taiyo-Yuden_NR-20xx
C_ISO: 100nF/500V; R_0402_1005Metric
C_MCU1: 100nF; R_0402_1005Metric
D1, D3: PRTR5V0U2X (TX); SOT-363_SC-70-6
D2, D4: PRTR5V0U2X (RX); SOT-363_SC-70-6
D5: PRTR5V0U2X (CAN); SOT-363_SC-70-6
J_CAM1: CSI_CLK/D0; JST_GH_BM04B-GHS-TBT_1x04-1MP_P1.25mm_Vertical
J_CAM2: CAM SDA/SCL/RST/3V3; JST_GH_BM04B-GHS-TBT_1x04-1MP_P1.25mm_Vertical
J_CAM_DS: DS_Camera_9P
J_CANFD: 5V/CANH/CANL/GND; JST_GH_BM04B-GHS-TBT_1x04-1MP_P1.25mm_Vertical
J_CHASSIS_R: 0R chassis bond; R_0402_1005Metric
J_ETH_IN: JST-GH 5P (shielded) Ethernet ring; JST_GH_SM05B-GHS-TB_1x05-1MP_P1.25mm_Horizontal
J_ETH_OUT: JST-GH 5P (shielded) Ethernet ring; JST_GH_SM05B-GHS-TB_1x05-1MP_P1.25mm_Horizontal
J_LASER: laser +5V/cathode; JST_SH_BM02B-SRSS-TB_1x02-1MP_P1.00mm_Vertical
J_LASER_DS: DS_Laser_2P
J_PWR: JST-GH 2P +5V/GND; JST_GH_BM02B-GHS-TBT_1x02-1MP_P1.25mm_Vertical
J_TOF: TFmini-S 5V/GND/TX/RX; JST_GH_BM04B-GHS-TBT_1x04-1MP_P1.25mm_Vertical
J_TOF_DS: DS_ToF_4P
MH1, MH2, MH3, MH4: (no value)
Q1: AO3400; SOT-23
R1: 100R; R_0402_1005Metric
R2: 10k; R_0402_1005Metric
T1, T2: Wurth 749010012A; Wurth_749010012A_10-100BASE-TX
U1: TI AM62A7; BGA484_18x18mm_PLACEHOLDER
U2: Microchip KSZ9477; QFN128_KSZ9477_PLACEHOLDER_14x14mm
U3: TI MSPM0G3507; MSPM0G3507_PLACEHOLDER_VSSOP28
U4: TI ISOW1044BDFMR; SOIC-16W_7.5x10.3mm_P1.27mm
U5: Infineon SLB9670; TPM_SLB9670_PLACEHOLDER_VQFN32
U_PMIC: TPS65219; PMIC_TPS65219_PLACEHOLDER_VQFN32
U_SOM: phyCORE-AM62x_PCM071; phyCORE-AM62x_PCM071_placement
Y1: 25MHz; Crystal_SMD_2016-2Pin_2.0x1.6mm

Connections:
+3V3: C_MCU1.1, J_CAM2.4, J_CAM_DS.8, U2.1, U3.1, U4.6, U5.1, U_PMIC.13
+5V: J_CANFD.1, J_LASER.1, J_LASER_DS.1, J_PWR.1, J_TOF.1, J_TOF_DS.1, U4.11, U_PMIC.1
CAM_RESET_N: J_CAM2.3, J_CAM_DS.7, U1.C3
CAM_SCL: J_CAM2.2, J_CAM_DS.6, U1.C2
CAM_SDA: J_CAM2.1, J_CAM_DS.5, U1.C1
CANFD_H: CMC5.2, D5.1, J_CANFD.2
CANFD_ISO_H: CMC5.1, U4.15
CANFD_ISO_L: CMC5.3, U4.14
CANFD_L: CMC5.4, D5.2, J_CANFD.3
CANFD_RX: U3.7, U4.4
CANFD_TX: U3.6, U4.2
CSI_CLK_N: J_CAM1.2, J_CAM_DS.2, U1.D2
CSI_CLK_P: J_CAM1.1, J_CAM_DS.1, U1.D1
CSI_D0_N: J_CAM1.4, J_CAM_DS.4, U1.D4
CSI_D0_P: J_CAM1.3, J_CAM_DS.3, U1.D3
ETH_IN_KSZ_RXN: T1.4, U2.29
ETH_IN_KSZ_RXP: T1.3, U2.28
ETH_IN_KSZ_TXN: T1.2, U2.27
ETH_IN_KSZ_TXP: T1.1, U2.26
ETH_IN_RXN: CMC2.4, D2.2, J_ETH_IN.5
ETH_IN_RXP: CMC2.2, D2.1, J_ETH_IN.4
ETH_IN_TXN: CMC1.4, D1.2, J_ETH_IN.3
ETH_IN_TXP: CMC1.2, D1.1, J_ETH_IN.2
ETH_IN_XFMR_RXN: CMC2.3, T1.8
ETH_IN_XFMR_RXP: CMC2.1, T1.7
ETH_IN_XFMR_TXN: CMC1.3, T1.6
ETH_IN_XFMR_TXP: CMC1.1, T1.5
ETH_OUT_KSZ_RXN: T2.4, U2.33
ETH_OUT_KSZ_RXP: T2.3, U2.32
ETH_OUT_KSZ_TXN: T2.2, U2.31
ETH_OUT_KSZ_TXP: T2.1, U2.30
ETH_OUT_RXN: CMC4.4, D4.2, J_ETH_OUT.5
ETH_OUT_RXP: CMC4.2, D4.1, J_ETH_OUT.4
ETH_OUT_TXN: CMC3.4, D3.2, J_ETH_OUT.3
ETH_OUT_TXP: CMC3.2, D3.1, J_ETH_OUT.2
ETH_OUT_XFMR_RXN: CMC4.3, T2.8
ETH_OUT_XFMR_RXP: CMC4.1, T2.7
ETH_OUT_XFMR_TXN: CMC3.3, T2.6
ETH_OUT_XFMR_TXP: CMC3.1, T2.5
GND: C_ISO.1, C_MCU1.2, D1.3, D2.3, D3.3, D4.3, J_CAM_DS.9, J_CANFD.4, J_CHASSIS_R.1, J_PWR.2, J_TOF.2, J_TOF_DS.2, Q1.2, R2.2, U1.A4, U2.3, U3.2, U4.1, U5.2, U_PMIC.2, Y1.2
LASER_CATHODE: J_LASER.2, J_LASER_DS.2, Q1.3
LASER_EN: R1.1, U3.19
LASER_GATE: Q1.1, R1.2, R2.1
PGND: C_ISO.2, D5.3, J_CHASSIS_R.2
PGND_SHIELD: J_ETH_IN.1, J_ETH_OUT.1
RGMII1_RXC: U1.P4, U2.23
RGMII1_RXCTL: U1.P5, U2.24
RGMII1_RXD0: U1.P6, U2.25
RGMII1_TXC: U1.P1, U2.20
RGMII1_TXCTL: U1.P2, U2.21
RGMII1_TXD0: U1.P3, U2.22
SW_SPI_CS: U2.7, U3.15
SW_SPI_MISO: U2.10, U3.18
SW_SPI_MOSI: U2.9, U3.17
SW_SPI_SCK: U2.8, U3.16
SW_XTAL_25M: U2.6, Y1.1
TPM_PIRQ: U3.14, U5.7
TPM_SPI_CS: U3.10, U5.3
TPM_SPI_MISO: U3.13, U5.6
TPM_SPI_MOSI: U3.12, U5.5
TPM_SPI_SCK: U3.11, U5.4
UART_A2M: U1.R1, U3.9
UART_M2A: U1.R2, U3.8
UART_TOF_RX: J_TOF.4, J_TOF_DS.4, U3.23
UART_TOF_TX: J_TOF.3, J_TOF_DS.3, U3.22
VDDR: U1.A3, U_PMIC.12
VDDSHV: U1.A2, U_PMIC.11
VDD_CORE: U1.A1, U_PMIC.10
